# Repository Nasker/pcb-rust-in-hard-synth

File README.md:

# RustInSynthPCB

Mainboard PCB for the **RinSynth** ESP32-S3 synthesizer — a standalone studio/performance
synth module with real analog I/O, DIN MIDI and an open firmware.

Companion firmware: [`rust-in-hard-synth`](https://github.com/Nasker/rust-in-hard-synth) (Rust, ESP-IDF).

## Overview

Single-PCB design. All user-facing components live on the front face; the ESP32-S3
development board is soldered as a receptor/socket on the **back** face.

| Block | Parts |
| :--- | :--- |
| MCU | ESP32-S3-DevKitC-1-**N16R8** (16 MB flash / 8 MB octal PSRAM), back-face mount |
| Audio in | TI PCM1860 stereo ADC (TSSOP-30) |
| Audio out | TI PCM5102A stereo DAC (TSSOP-20) |
| Jacks | 4× 6.35 mm right-angle jacks (Neutrik-clone footprint, 6 pins, no locating pegs) |
| MIDI | DIN-5 MIDI **input** (H11L1 optocoupler) — consumer only, no MIDI out |
| Controls | 4× ACP CA9 SMD potentiometers, 4× Panasonic EVQPU tactile switches, Bourns PEC11S encoder w/ push |
| Display | 1.3" 128×64 SPI OLED |
| Storage | microSD (Würth 693072010801) |
| Power | LP5907-3.3 LDO + ferrite filtering for the analog rail |

I2S clocks use single-resistor source termination at the MCU (option-B topology);
GPIO33–37 are avoided because they serve the octal PSRAM bus.

## Repo layout

```
RustInSynthPCB.kicad_pro / .kicad_sch / .kicad_pcb   # project, root sheet, board
ui.kicad_sch / audio.kicad_sch / midi.kicad_sch / mcu.kicad_sch   # subsheets
Local_Libraries/     # project symbols, footprints and 3D models
Enclosure/           # enclosure CAD + STEP export
JLC_BOM.csv          # JLCPCB/LCSC-sourced BOM (C-numbers, assembly notes)
Images/, Schematics/ # renders & reference PDFs
```

## Status

Rev 1 — routed, DRC clean (0 unconnected / 0 shorts). Work-in-progress; see the
`develop` branch for current changes.

## License

MIT — see [LICENSE.txt](LICENSE.txt)

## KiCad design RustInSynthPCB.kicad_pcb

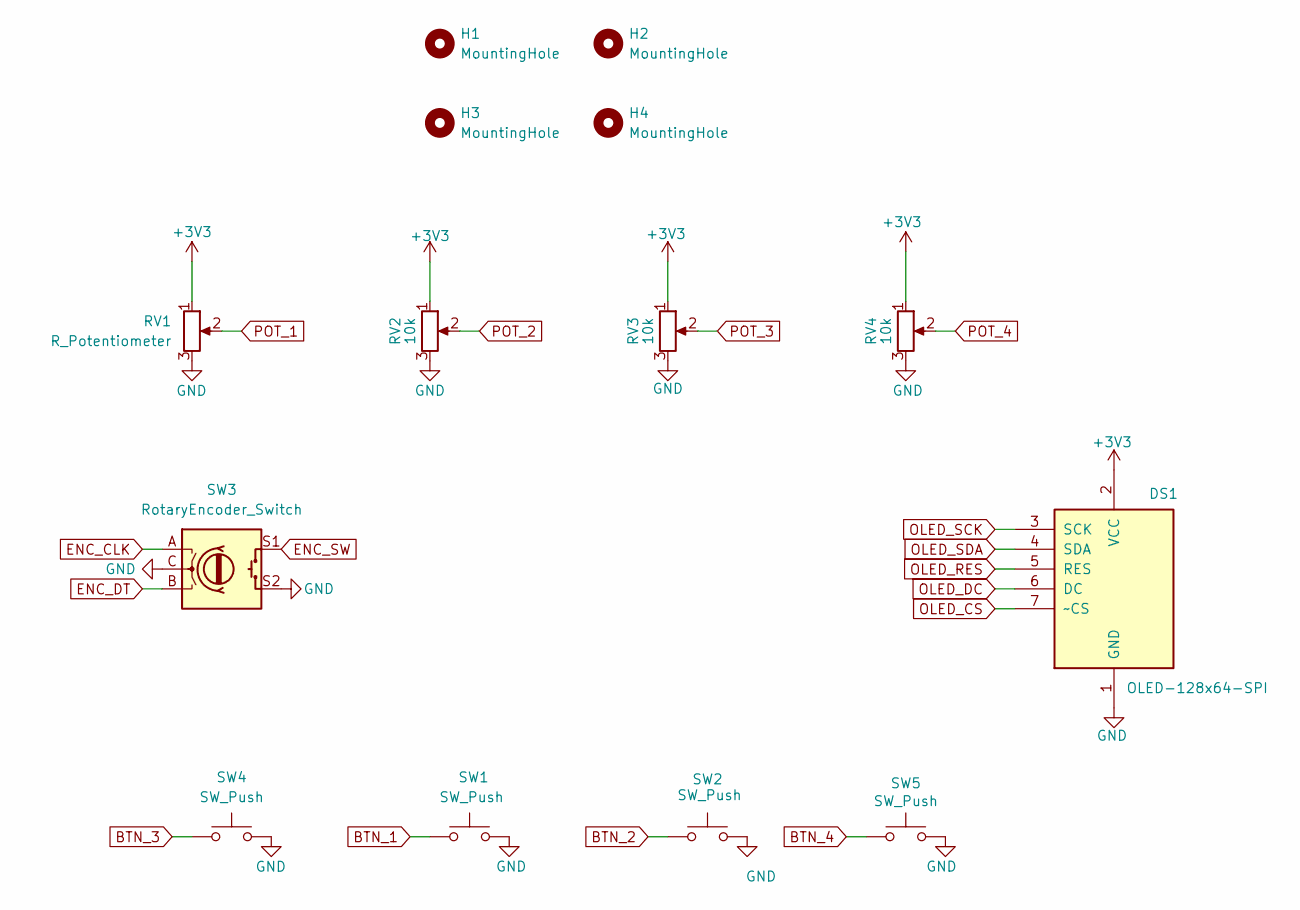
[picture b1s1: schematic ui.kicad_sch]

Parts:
DS1: OLED-128x64-SPI; OLED-1.3inch-128x64-SPI-SMD
H1, H2, H3, H4: MountingHole; TestPoint_Plated_Hole_D3.0mm
RV1: R_Potentiometer; Potentiometer_ACP_CA9-VSMD_Vertical
RV2, RV3, RV4: 10k; Potentiometer_ACP_CA9-VSMD_Vertical
SW1, SW2, SW4, SW5: SW_Push; Panasonic_EVQPUM_EVQPUD
SW3: RotaryEncoder_Switch; RotaryEncoder_EC12E-SMD

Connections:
+3V3: DS1.2 (VCC), RV1.1, RV2.1, RV3.1, RV4.1; also elsewhere on the board
BTN_1: SW1.1; also elsewhere on the board
BTN_2: SW2.1; also elsewhere on the board
BTN_3: SW4.1; also elsewhere on the board
BTN_4: SW5.1; also elsewhere on the board
ENC_CLK: SW3.A; also elsewhere on the board
ENC_DT: SW3.B; also elsewhere on the board
ENC_SW: SW3.S1; also elsewhere on the board
GND: DS1.1 (GND), RV1.3, RV2.3, RV3.3, RV4.3, SW1.2, SW2.2, SW3.C, SW3.S2, SW4.2, SW5.2; also elsewhere on the board
OLED_CS: DS1.7 (~CS); also elsewhere on the board
OLED_DC: DS1.6 (DC); also elsewhere on the board
OLED_RES: DS1.5 (RES); also elsewhere on the board
OLED_SCK: DS1.3 (SCK); also elsewhere on the board
OLED_SDA: DS1.4 (SDA); also elsewhere on the board
POT_1: RV1.2; also elsewhere on the board
POT_2: RV2.2; also elsewhere on the board
POT_3: RV3.2; also elsewhere on the board
POT_4: RV4.2; also elsewhere on the board

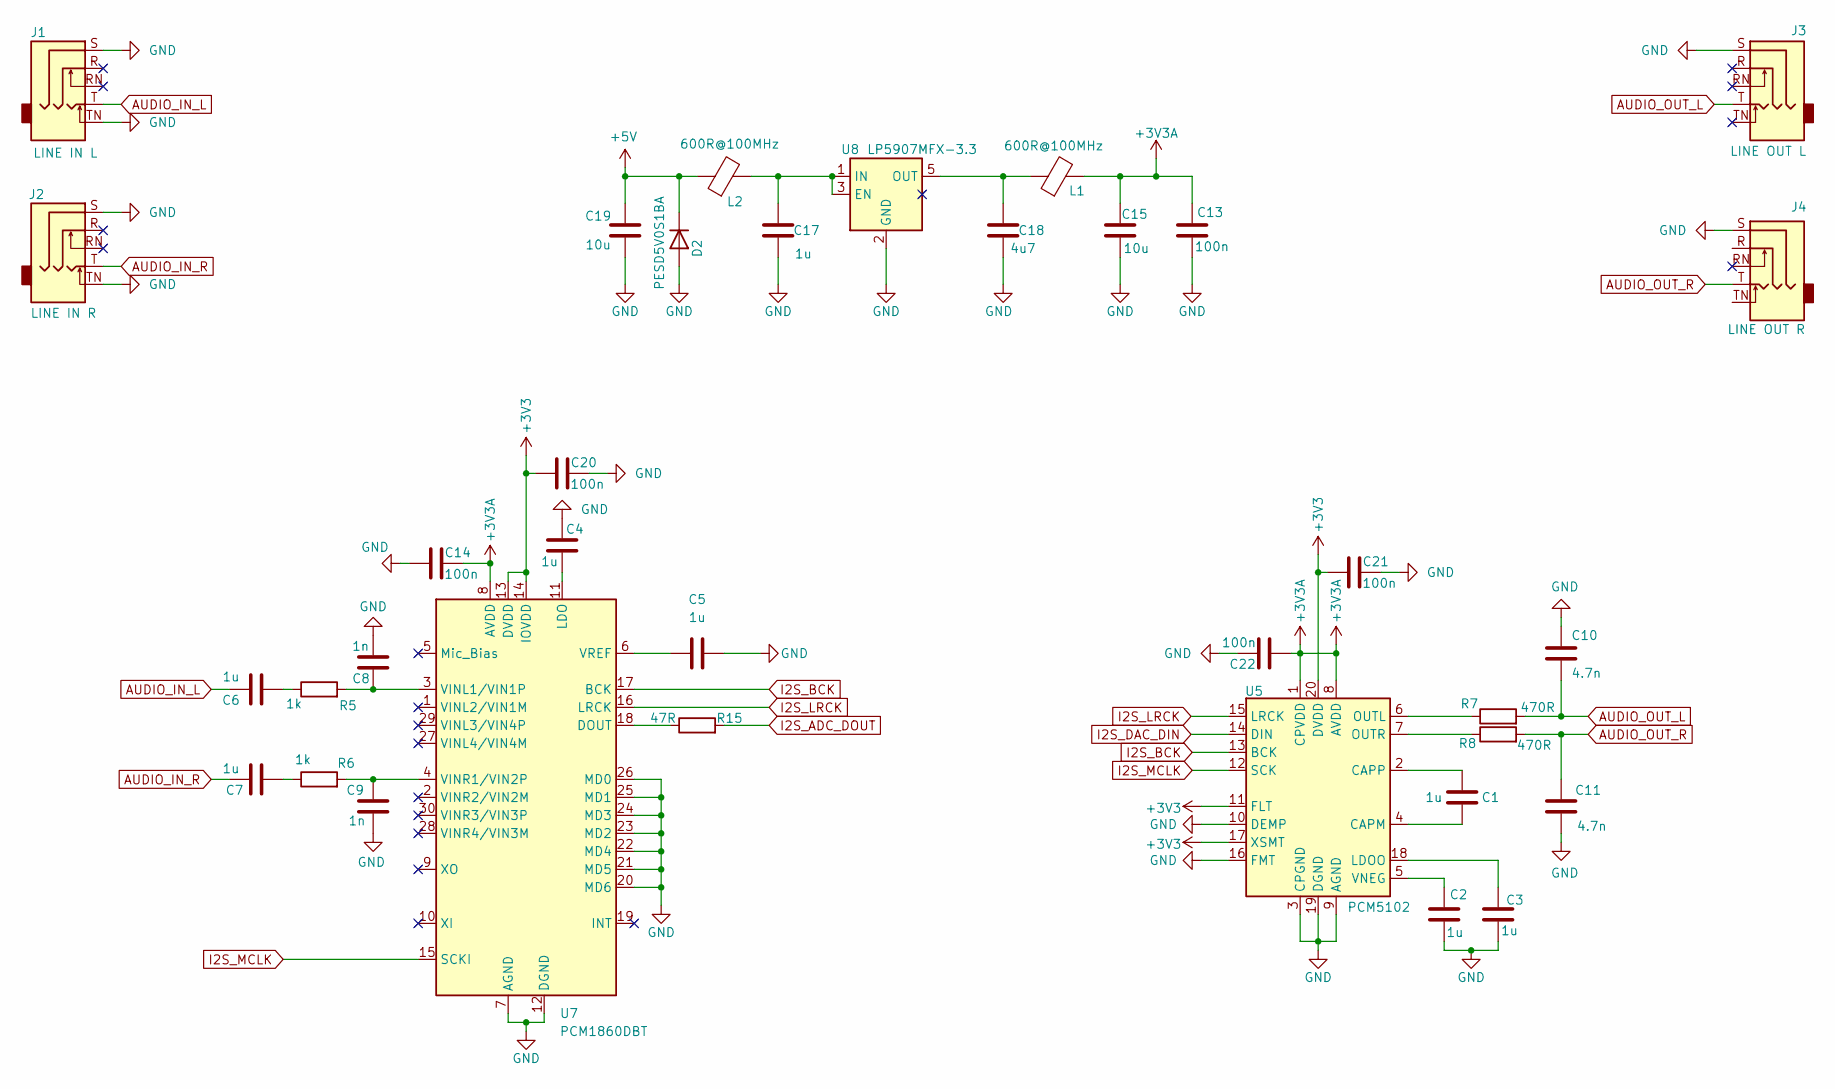
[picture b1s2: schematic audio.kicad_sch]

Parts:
C1, C2, C3, C4, C5, C6, C7, C17: 1u; C_0603_1608Metric
C8, C9: 1n; C_0603_1608Metric
C10, C11: 4.7n; C_0603_1608Metric
C13, C14, C20, C21, C22: 100n; C_0603_1608Metric
C15, C19: 10u; C_0603_1608Metric
C18: 4u7; C_0603_1608Metric
D2: PESD5V0S1BA; D_SOD-323
J1: LINE IN L; Jack_6.35mm_Neutrik_NRJ6HF-1_Horizontal
J2: LINE IN R; Jack_6.35mm_Neutrik_NRJ6HF-1_Horizontal
J3: LINE OUT L; Jack_6.35mm_Neutrik_NRJ6HF-1_Horizontal
J4: LINE OUT R; Jack_6.35mm_Neutrik_NRJ6HF-1_Horizontal
L1, L2: 600R@100MHz; L_0603_1608Metric
R5, R6: 1k; R_0603_1608Metric
R7, R8: 470R; R_0603_1608Metric
R15: 47R; R_0603_1608Metric
U5: PCM5102; TSSOP-20_4.4x6.5mm_P0.65mm
U7: PCM1860DBT; TSSOP-30_4.4x7.8mm_P0.5mm
U8: LP5907MFX-3.3; SOT-23-5

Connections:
+3V3: C20.2, C21.2, U5.11 (FLT), U5.17 (XSMT), U5.20 (DVDD), U7.13 (DVDD), U7.14 (IOVDD); also elsewhere on the board
+3V3A: C13.1, C14.1, C15.1, C22.2, L1.2, U5.1 (CPVDD), U5.8 (AVDD), U7.8 (AVDD)
+5V: C19.1, D2.1 (K), L2.1; also elsewhere on the board
AUDIO_IN_L: C6.1, J1.T
AUDIO_IN_R: C7.1, J2.T
AUDIO_OUT_L: C10.1, J3.T, R7.2
AUDIO_OUT_R: C11.1, J4.T, R8.2
GND: C2.2, C3.2, C4.1, C5.2, C8.2, C9.2, C10.2, C11.2, C13.2, C14.2, C15.2, C17.2, C18.2, C19.2, C20.1, C21.1, C22.1, D2.2 (A), J1.S, J1.TN, J2.S, J2.TN, J3.S, J4.S, U5.3 (CPGND), U5.9 (AGND), U5.10 (DEMP), U5.16 (FMT), U5.19 (DGND), U7.7 (AGND), U7.12 (DGND), U7.20 (MD6), U7.21 (MD5), U7.22 (MD4), U7.23 (MD2), U7.24 (MD3), U7.25 (MD1), U7.26 (MD0), U8.2 (GND); also elsewhere on the board
I2S_ADC_DOUT: R15.2; also elsewhere on the board
I2S_BCK: U5.13 (BCK), U7.17 (BCK); also elsewhere on the board
I2S_DAC_DIN: U5.14 (DIN); also elsewhere on the board
I2S_LRCK: U5.15 (LRCK), U7.16 (LRCK); also elsewhere on the board
I2S_MCLK: U5.12 (SCK), U7.15 (SCKI); also elsewhere on the board
unnamed: C6.2, R5.1
unnamed: C7.2, R6.1
unnamed: C1.2, U5.4 (CAPM)
unnamed: C1.1, U5.2 (CAPP)
unnamed: C3.1, U5.18 (LDOO)
unnamed: R7.1, U5.6 (OUTL)
unnamed: R8.1, U5.7 (OUTR)
unnamed: C2.1, U5.5 (VNEG)
unnamed: R15.1, U7.18 (DOUT)
unnamed: C4.2, U7.11 (LDO)
unnamed: C8.1, R5.2, U7.3 (VINL1/VIN1P)
unnamed: C9.1, R6.2, U7.4 (VINR1/VIN2P)
unnamed: C5.1, U7.6 (VREF)
unnamed: C17.1, L2.2, U8.1 (IN), U8.3 (EN)
unnamed: C18.1, L1.1, U8.5 (OUT)

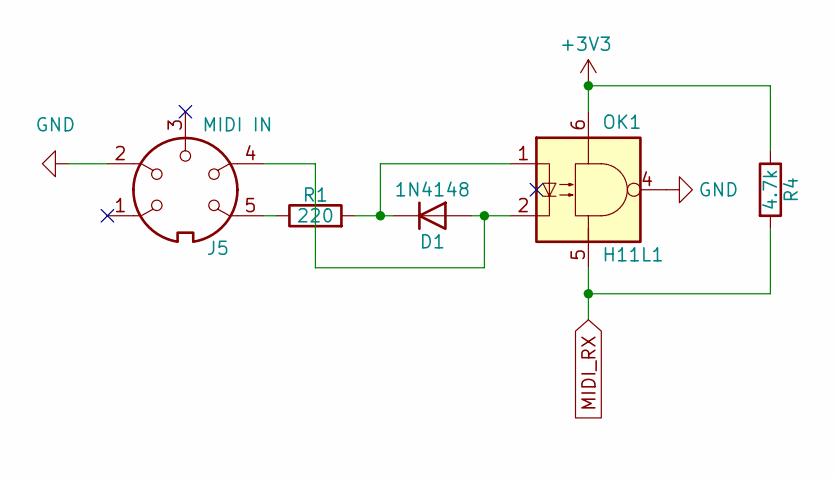
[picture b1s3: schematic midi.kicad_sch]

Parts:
D1: 1N4148; D_SOD-323
J5: MIDI IN; DIN-5-MIDI-RA
OK1: H11L1; SMDIP-6_W9.53mm
R1: 220; R_0603_1608Metric
R4: 4.7k; R_0603_1608Metric

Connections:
+3V3: OK1.6, R4.1; also elsewhere on the board
GND: J5.2, OK1.4; also elsewhere on the board
MIDI_RX: OK1.5, R4.2; also elsewhere on the board
unnamed: D1.2 (A), J5.4, OK1.2
unnamed: D1.1 (K), OK1.1, R1.2
unnamed: J5.5, R1.1

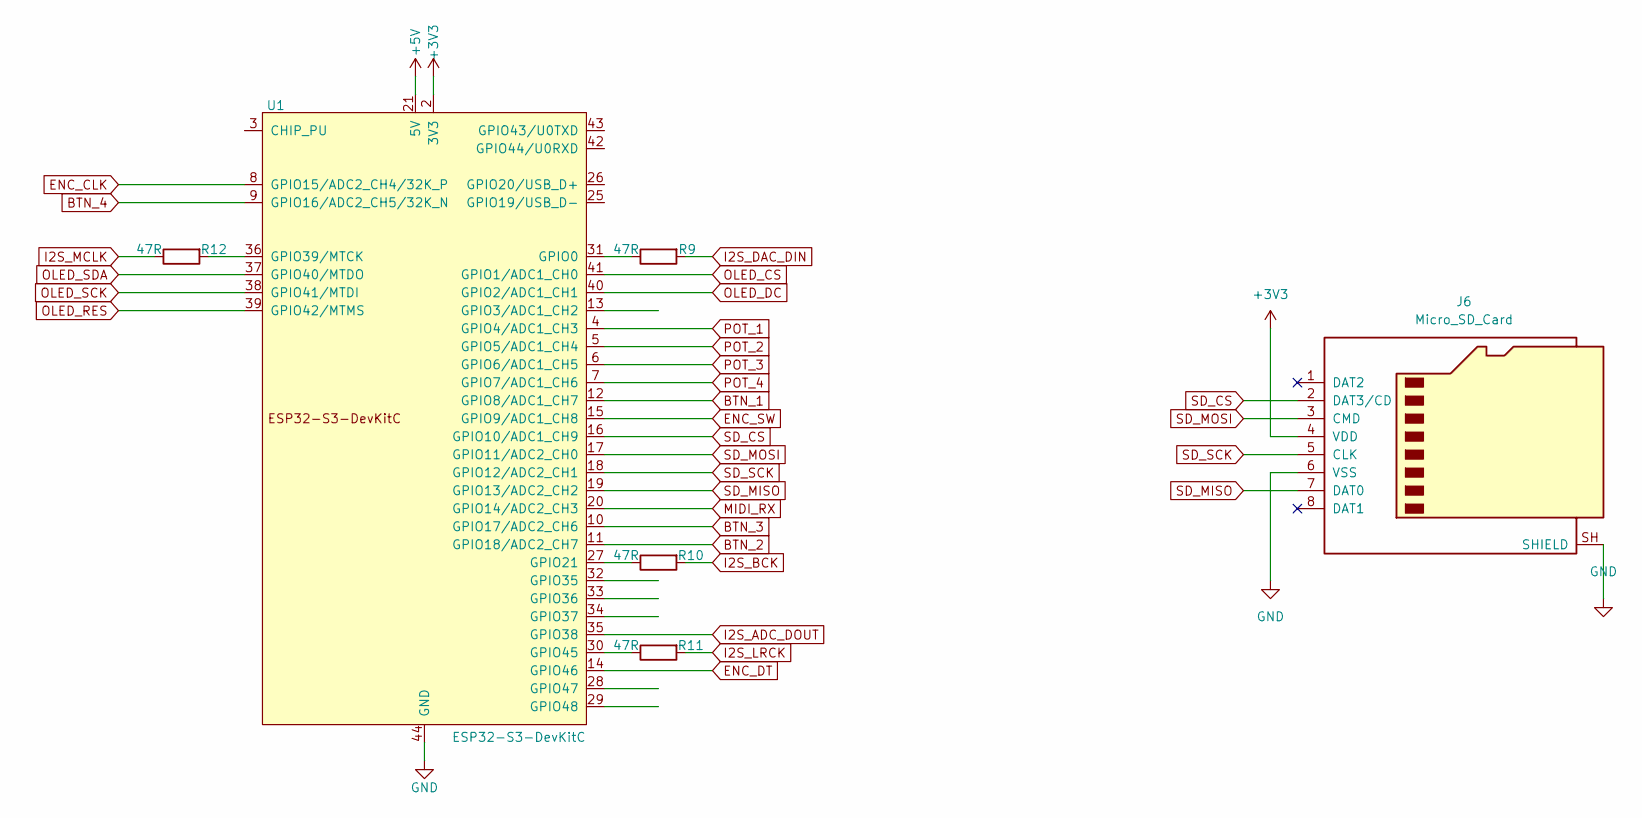
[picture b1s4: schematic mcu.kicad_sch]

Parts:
J6: Micro_SD_Card; microSD_HC_Wuerth_693072010801
R9, R10, R11, R12: 47R; R_0603_1608Metric
U1: ESP32-S3-DevKitC; ESP32-S3-DevKitC-1-N16R8-SMD

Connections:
+3V3: J6.4 (VDD), U1.1 (3V3), U1.2 (3V3); also elsewhere on the board
+5V: U1.21 (5V); also elsewhere on the board
BTN_1: U1.12 (GPIO8/ADC1_CH7); also elsewhere on the board
BTN_2: U1.11 (GPIO18/ADC2_CH7); also elsewhere on the board
BTN_3: U1.10 (GPIO17/ADC2_CH6); also elsewhere on the board
BTN_4: U1.9 (GPIO16/ADC2_CH5/32K_N); also elsewhere on the board
ENC_CLK: U1.8 (GPIO15/ADC2_CH4/32K_P); also elsewhere on the board
ENC_DT: U1.14 (GPIO46); also elsewhere on the board
ENC_SW: U1.15 (GPIO9/ADC1_CH8); also elsewhere on the board
GND: J6.6 (VSS), J6.SH (SHIELD), U1.22 (GND), U1.23 (GND), U1.24 (GND), U1.44 (GND); also elsewhere on the board
I2S_ADC_DOUT: U1.35 (GPIO38); also elsewhere on the board
I2S_BCK: R10.2; also elsewhere on the board
I2S_DAC_DIN: R9.2; also elsewhere on the board
I2S_LRCK: R11.2; also elsewhere on the board
I2S_MCLK: R12.1; also elsewhere on the board
MIDI_RX: U1.20 (GPIO14/ADC2_CH3); also elsewhere on the board
unnamed: R9.1, U1.31 (GPIO0)
unnamed: R10.1, U1.27 (GPIO21)
unnamed: R12.2, U1.36 (GPIO39/MTCK)
unnamed: R11.1, U1.30 (GPIO45)
OLED_CS: U1.41 (GPIO1/ADC1_CH0); also elsewhere on the board
OLED_DC: U1.40 (GPIO2/ADC1_CH1); also elsewhere on the board
OLED_RES: U1.39 (GPIO42/MTMS); also elsewhere on the board
OLED_SCK: U1.38 (GPIO41/MTDI); also elsewhere on the board
OLED_SDA: U1.37 (GPIO40/MTDO); also elsewhere on the board
POT_1: U1.4 (GPIO4/ADC1_CH3); also elsewhere on the board
POT_2: U1.5 (GPIO5/ADC1_CH4); also elsewhere on the board
POT_3: U1.6 (GPIO6/ADC1_CH5); also elsewhere on the board
POT_4: U1.7 (GPIO7/ADC1_CH6); also elsewhere on the board
SD_CS: J6.2 (DAT3/CD), U1.16 (GPIO10/ADC1_CH9)
SD_MISO: J6.7 (DAT0), U1.19 (GPIO13/ADC2_CH2)
SD_MOSI: J6.3 (CMD), U1.17 (GPIO11/ADC2_CH0)
SD_SCK: J6.5 (CLK), U1.18 (GPIO12/ADC2_CH1)

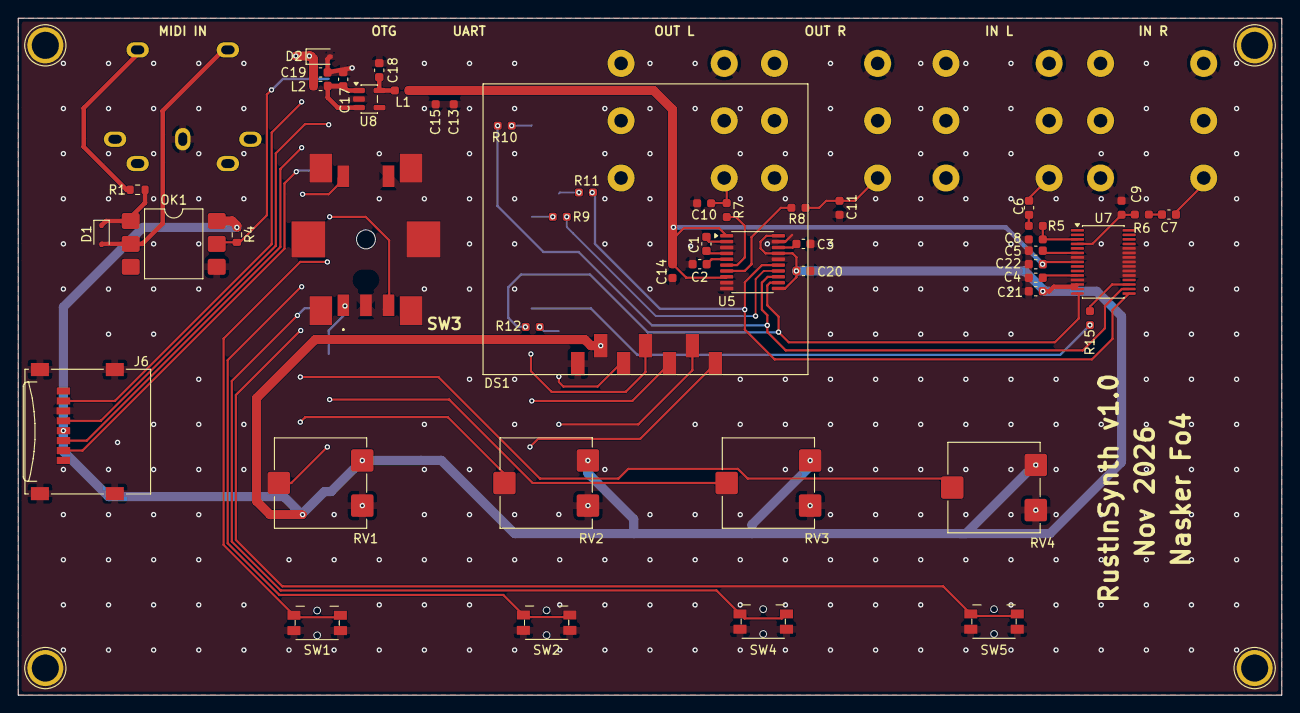
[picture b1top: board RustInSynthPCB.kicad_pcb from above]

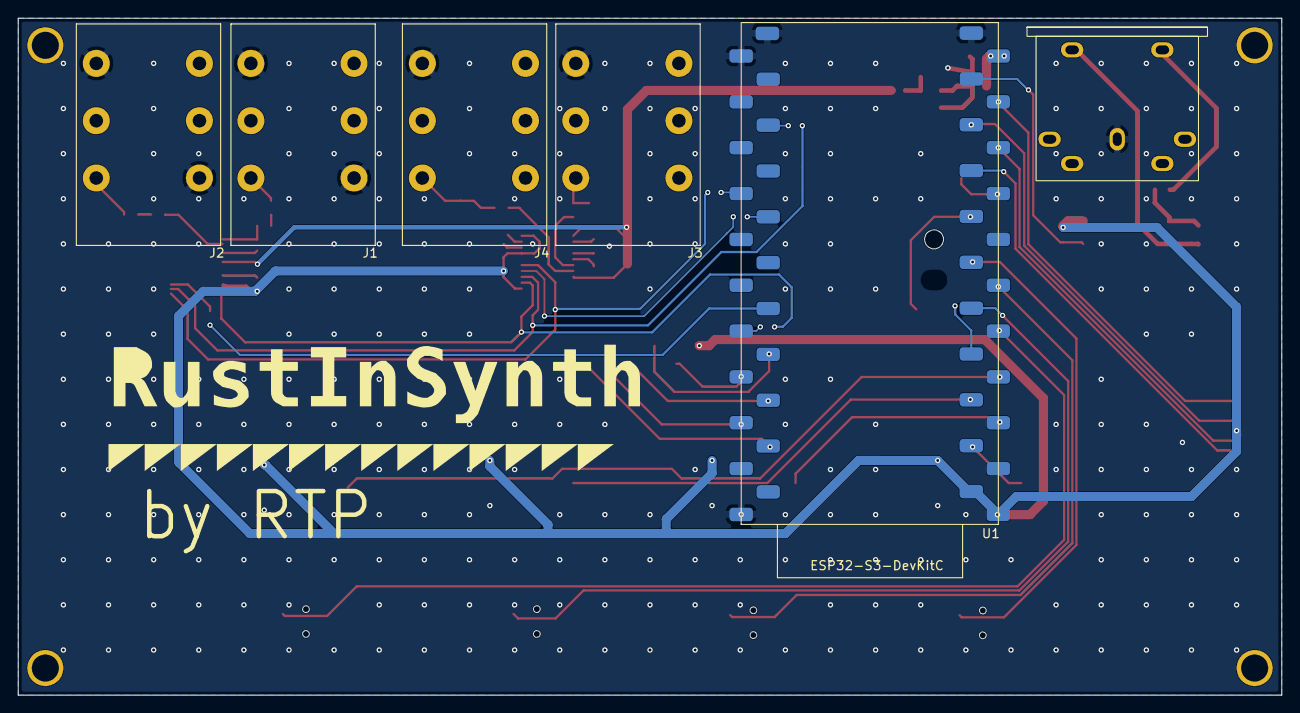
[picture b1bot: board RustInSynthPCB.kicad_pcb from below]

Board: 2 copper layers, 140.0 x 75.0 mm, 61 parts (7 on the bottom side), 56 nets.

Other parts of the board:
LOGO1: Logo_RustInSynth_SilkS

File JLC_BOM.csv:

Comment,Designator,Footprint,LCSC Part #,Manufacturer Part #,Note,Link
1uF 25V X5R 0603,"C1,C2,C3,C4,C5,C6,C7,C17",C_0603_1608Metric,C15849,CL10A105KO8NNNC,,
100nF 50V X7R 0603,"C13,C14,C20,C21,C22",C_0603_1608Metric,C14663,CL10B104KB8NNNC,,
10uF 10V X5R 0603,"C15,C19",C_0603_1608Metric,C19702,CL10A106KP8NNNC,10V rating fine on 3.3V,
4.7uF 10V X5R 0603,C18,C_0603_1608Metric,C1705,CL10A475KP8NNNC,10V rating fine on 3.3V,
1nF 50V X7R 0603,"C8,C9",C_0603_1608Metric,C7503505,CGA0603X7R102K500JT,,
4.7nF 50V X7R 0603,"C10,C11",C_0603_1608Metric,C7078000,AS0603KRX7R9BB472,,
220R 1% 0603,R1,R_0603_1608Metric,C107696,RC0603FR-07220RL,,
4.7k 1% 0603,R4,R_0603_1608Metric,C99782,RC0603FR-074K7L,,
1k 1% 0603,"R5,R6",R_0603_1608Metric,C21190,RC0603FR-071KL,,
470R 1% 0603,"R7,R8",R_0603_1608Metric,C114669,RC0603FR-07470RL,,
47R 1% 0603,"R9,R10,R11,R12,R15",R_0603_1608Metric,C23162,RC0603FR-0747RL,,
1N4148WS SOD-323,D1,D_SOD-323,C2128,1N4148WS,,
PESD5V0S1BA SOD-323,D2,D_SOD-323,C5158048,PESD5V0S1BA,,
600R@100MHz ferrite 0603,"L1,L2",L_0603_1608Metric,C1002,BLM18AG601SN1D,,
LP5907-3.3 SOT-23-5,U8,SOT-23-5,C80670,LP5907MFX-3.3/NOPB,,
PCM5102A TSSOP-20,U5,TSSOP-20_4.4x6.5mm_P0.65mm,C107671,PCM5102APWR,,
PCM1860 TSSOP-30,U7,TSSOP-30_4.4x7.8mm_P0.5mm,C1520799,PCM1860DBT,,
H11L1 SMD-6P,OK1,SMDIP-6_W9.53mm,C47361223,H11L1(SL)(T1)-GV,verify gull-wing footprint fit,
EVQPUD02K tactile,"SW1,SW2,SW4,SW5",Panasonic_EVQPUM_EVQPUD,C388885,EVQPUD02K,,
ESP32-S3-DevKitC-1-N16R8,U1,ESP32-S3-DevKitC-1-N16R8-SMD,,ESP32-S3-DEVKITC-1-N16R8,N16R8 dual USB-C devkit,https://www.aliexpress.com/i/3256806053755799.html
OLED 1.3in 128x64 SPI,DS1,OLED-1.3inch-128x64-SPI-SMD,,,SH1106/SSD1309 7pin SPI (~$2-4),https://www.aliexpress.com/w/wholesale-1.3-inch-oled-128x64-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
10k lin pot CA9-VSMD,"RV1,RV2,RV3,RV4",Potentiometer_ACP_CA9-VSMD_Vertical,,ACP CA9-VSMD-10KA2020,CA9VSMD-10K; not on LCSC,https://www.tme.eu/html/EN/acp-trimmers-ca9-series/ramka_289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
Rotary encoder 12mm w/ push switch,SW3,RotaryEncoder_Bourns_PEC11S-SMD,C5362681,PEC11S-929K-S0015,true SMD on LCSC (JLC-assemblable),
6.35mm jack 6-pin stereo TH,"J1,J2,J3,J4",Jack_6.35mm_Clone_Horizontal,C309285,PJ-625,pad geometry VERIFIED vs datasheet (2x3 6.35mm pitch 11.4mm rows); confirm T/R/S pin order vs own clones,
DIN-5 MIDI RA,J5,DIN-5-MIDI-RA,,,TEDIN-D501 $0.32 - verify pin pattern vs footprint,https://www.taydaelectronics.com/5-pin-midi-connector-female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
microSD socket Wurth hinge,J6,microSD_HC_Wuerth_693072010801,,693072010801,732-3820-1-ND ($6.10); LCSC alt C53223921 needs different footprint,https://www.digikey.com/en/products/detail/wurth-elektronik/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
Mounting hole D3,"H1,H2,H3,H4",TestPoint_Plated_Hole_D3.0mm,,,mechanical only,

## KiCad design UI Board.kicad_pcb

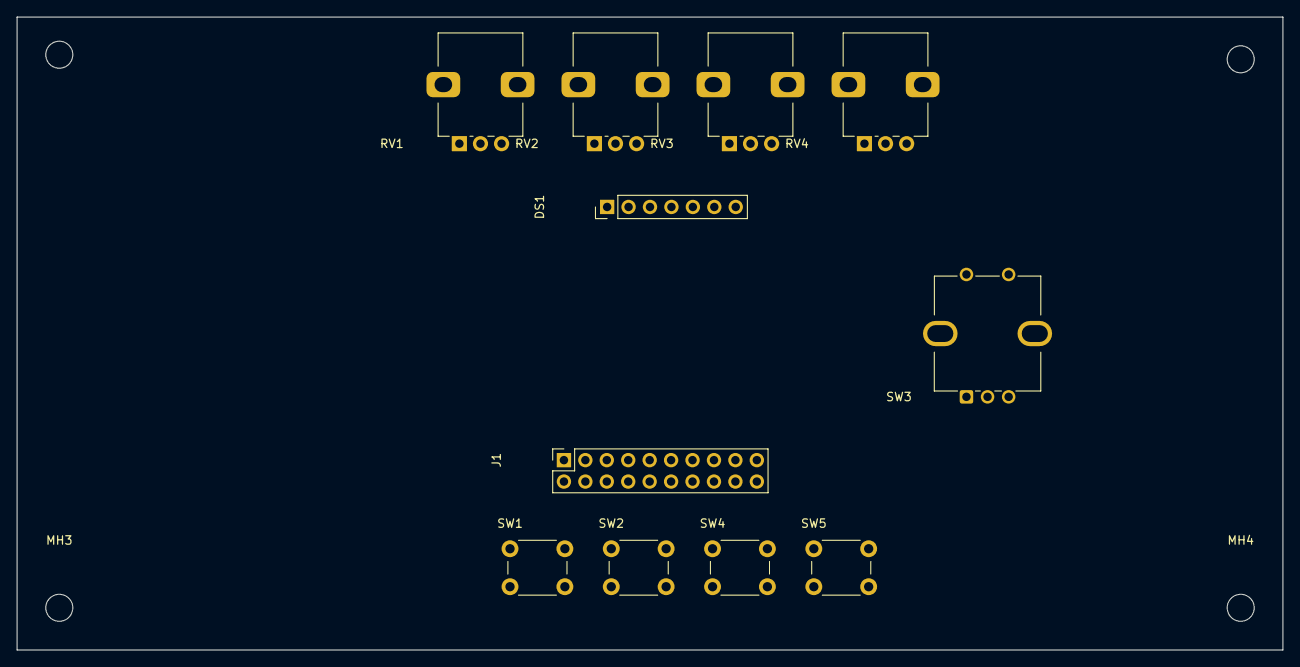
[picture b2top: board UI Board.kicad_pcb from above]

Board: 2 copper layers, 150.0 x 75.0 mm, 15 parts (0 on the bottom side), 4 nets, no tracks yet.

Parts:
DS1: OLED; PinHeader_1x07_P2.54mm_Vertical
J1: MAIN_CONN; PinSocket_2x10_P2.54mm_Vertical
MH1, MH2, MH3, MH4: M3; MountingHole_3.2mm_M3
RV1, RV2, RV3, RV4: 10k; Potentiometer_Alps_RK09K_Single_Vertical
SW1: BTN_1; SW_PUSH_6mm
SW2: BTN_2; SW_PUSH_6mm
SW3: ENCODER; RotaryEncoder_Bourns_Vertical_PEC12R-3x17F-Sxxxx
SW4: BTN_3; SW_PUSH_6mm
SW5: BTN_4; SW_PUSH_6mm

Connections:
ENC_CLK: J1.11, SW3.A
ENC_DT: J1.12, SW3.B
ENC_SW: J1.13, SW3.S1
GND: J1.2, J1.19, J1.20, SW3.C, SW3.S2
